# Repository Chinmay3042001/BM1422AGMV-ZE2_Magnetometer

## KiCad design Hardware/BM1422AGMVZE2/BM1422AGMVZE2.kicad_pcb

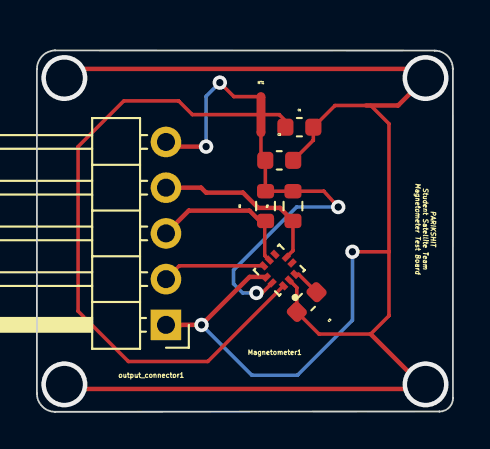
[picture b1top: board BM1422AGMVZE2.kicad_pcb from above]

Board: 2 copper layers, 23.1 x 20.8 mm, 8 parts (0 on the bottom side), 8 nets.

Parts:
C1, C3: 1uF0; C_0603_1608Metric
C2: 0uF01; C_0603_1608Metric
Magnetometer1: BM1422AGMV-ZE2; PQFN45P200X200X100-10N
NT1: NetTie_3_Tee; NetTie-3_SMD_Pad0.5mm
R1, R2: 10k; R_0603_1608Metric
output_connector1: Conn_01x05_MountingPin; PinHeader_1x05_P2.54mm_Horizontal

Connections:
/AVDD: C1.1, Magnetometer1.1 (AVDD), NT1.2
/DRDY: Magnetometer1.8 (DRDY), output_connector1.2
/DVDD: C2.1, Magnetometer1.10 (DVDD), NT1.3, R1.2, R2.2
/GND: C1.2, C2.2, C3.2, Magnetometer1.2 (GND), Magnetometer1.9 (ADDR), output_connector1.1
/SCL: Magnetometer1.7 (SCL), R2.1, output_connector1.3
/SDA: Magnetometer1.5 (SDA), R1.1, output_connector1.4
/VDD: NT1.1, output_connector1.5
/VREG: C3.1, Magnetometer1.3 (VREG)

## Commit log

2022-08-26 Magnetometer Test PCB
2022-08-26 GND via has exposed copper now
